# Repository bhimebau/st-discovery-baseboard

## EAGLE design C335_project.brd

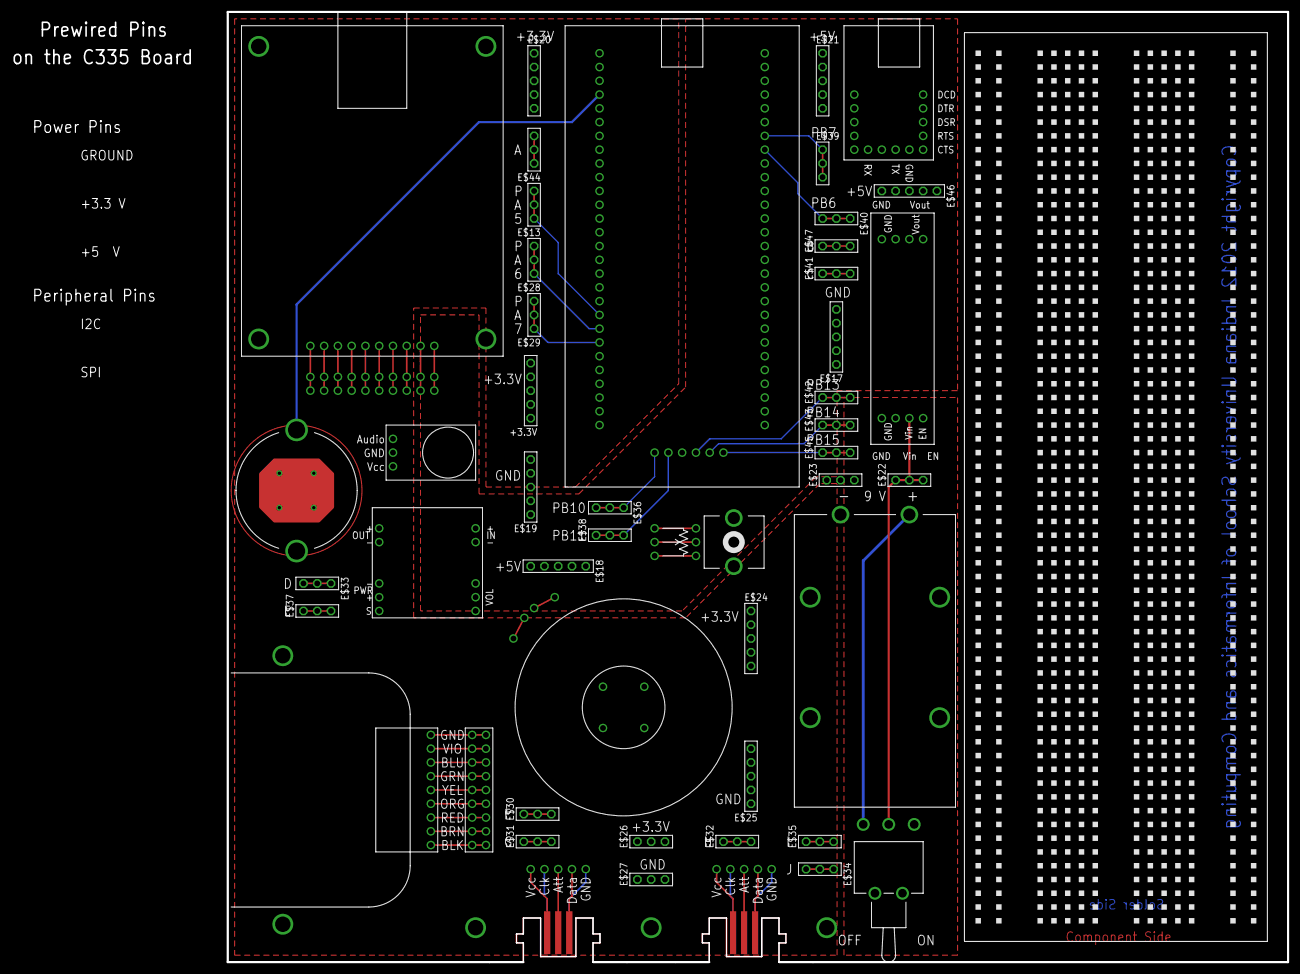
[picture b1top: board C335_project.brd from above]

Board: 2 copper layers, 195.6 x 175.3 mm, 48 parts (0 on the bottom side), 25 nets.

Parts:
+3.3V: SSW-105-02-S-S
E$1: TFT_LCD
E$2: USB_SER
E$3: STM32
E$4: PROTOBRD
E$5: MIC
E$6, E$7: NUNCHUK_CONN
E$8: SALEAE_HDR
E$9: AUDIO_AMP
E$10: SPEAKER
E$11: PWR_REG
E$12: BATT_9V
E$13, E$22, E$23, E$26, E$27, E$28, E$29, E$30, E$31, E$32, E$33, E$34, E$35, E$36, E$37, E$38, E$39, E$40, E$41, E$42, E$43, E$44, E$45, E$47: SSW-103-02-S-S
E$14: POT
E$15: SW_TOG_HOR_PC
E$16: BATT_CR20
E$17, E$18, E$19, E$20, E$21, E$24, E$25, E$46: SSW-105-02-S-S

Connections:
3.3V: +3.3V.1, +3.3V.2, +3.3V.3, +3.3V.4, +3.3V.5, E$3.P$26, E$5.3, E$6.1, E$7.1, E$9.2, E$20.1, E$20.2, E$20.3, E$20.4, E$20.5, E$24.1, E$24.2, E$24.3, E$24.4, E$24.5, E$26.1, E$26.2, E$26.3
5V: E$1.P$10, E$1.P$20, E$1.P$30, E$3.P$88, E$11.P$7, E$11.P$8, E$18.1, E$18.2, E$18.3, E$18.4, E$18.5, E$21.1, E$21.2, E$21.3, E$21.4, E$21.5, E$46.1, E$46.2, E$46.3, E$46.4, E$46.5
+9V: E$11.P$3, E$15.3, E$22.1, E$22.2, E$22.3
GND: E$1.P$1, E$1.P$11, E$1.P$21, E$2.5, E$3.P$1, E$3.P$28, E$3.P$63, E$3.P$90, E$5.1, E$6.P$1, E$7.P$1, E$8.5, E$8.14, E$8.25, E$9.3, E$11.P$1, E$11.P$2, E$11.P$5, E$11.P$6, E$12.2, E$16.3, E$16.4, E$16.5, E$16.6, E$17.1, E$17.2, E$17.3, E$17.4, E$17.5, E$19.1, E$19.2, E$19.3, E$19.4, E$19.5, E$23.1, E$23.2, E$23.3, E$25.1, E$25.2, E$25.3, E$25.4, E$25.5, E$27.1, E$27.2, E$27.3
S$2: E$12.1, E$15.4
S$3: E$47.1, E$47.3
S$6: E$35.1, E$35.3
S$7: E$34.1, E$34.3
S$10: E$32.1, E$32.3
S$11: E$31.1, E$31.3
S$12: E$30.1, E$30.3
S$13: E$33.1, E$33.3
S$14: E$3.P$9, E$13.1, E$13.3
S$16: E$3.P$7, E$29.1, E$29.3
S$17: E$37.1, E$37.3
S$18: E$3.P$57, E$36.1, E$36.3
S$19: E$3.P$58, E$38.1, E$38.3
S$20: E$3.P$60, E$42.1, E$42.3
S$21: E$41.1, E$41.3
S$22: E$3.P$84, E$39.1, E$39.2, E$39.3
S$23: E$3.P$83, E$40.1, E$40.2, E$40.3
S$24: E$3.P$8, E$28.1, E$28.3
S$25: E$3.P$61, E$43.1, E$43.3
S$26: E$44.1, E$44.3
S$27: E$3.P$62, E$45.1, E$45.3

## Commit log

2012-11-28 initial check-in from the migration

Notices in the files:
C335_project.brd:
Copyright 2012 Indiana University School of Informatics and Computing
